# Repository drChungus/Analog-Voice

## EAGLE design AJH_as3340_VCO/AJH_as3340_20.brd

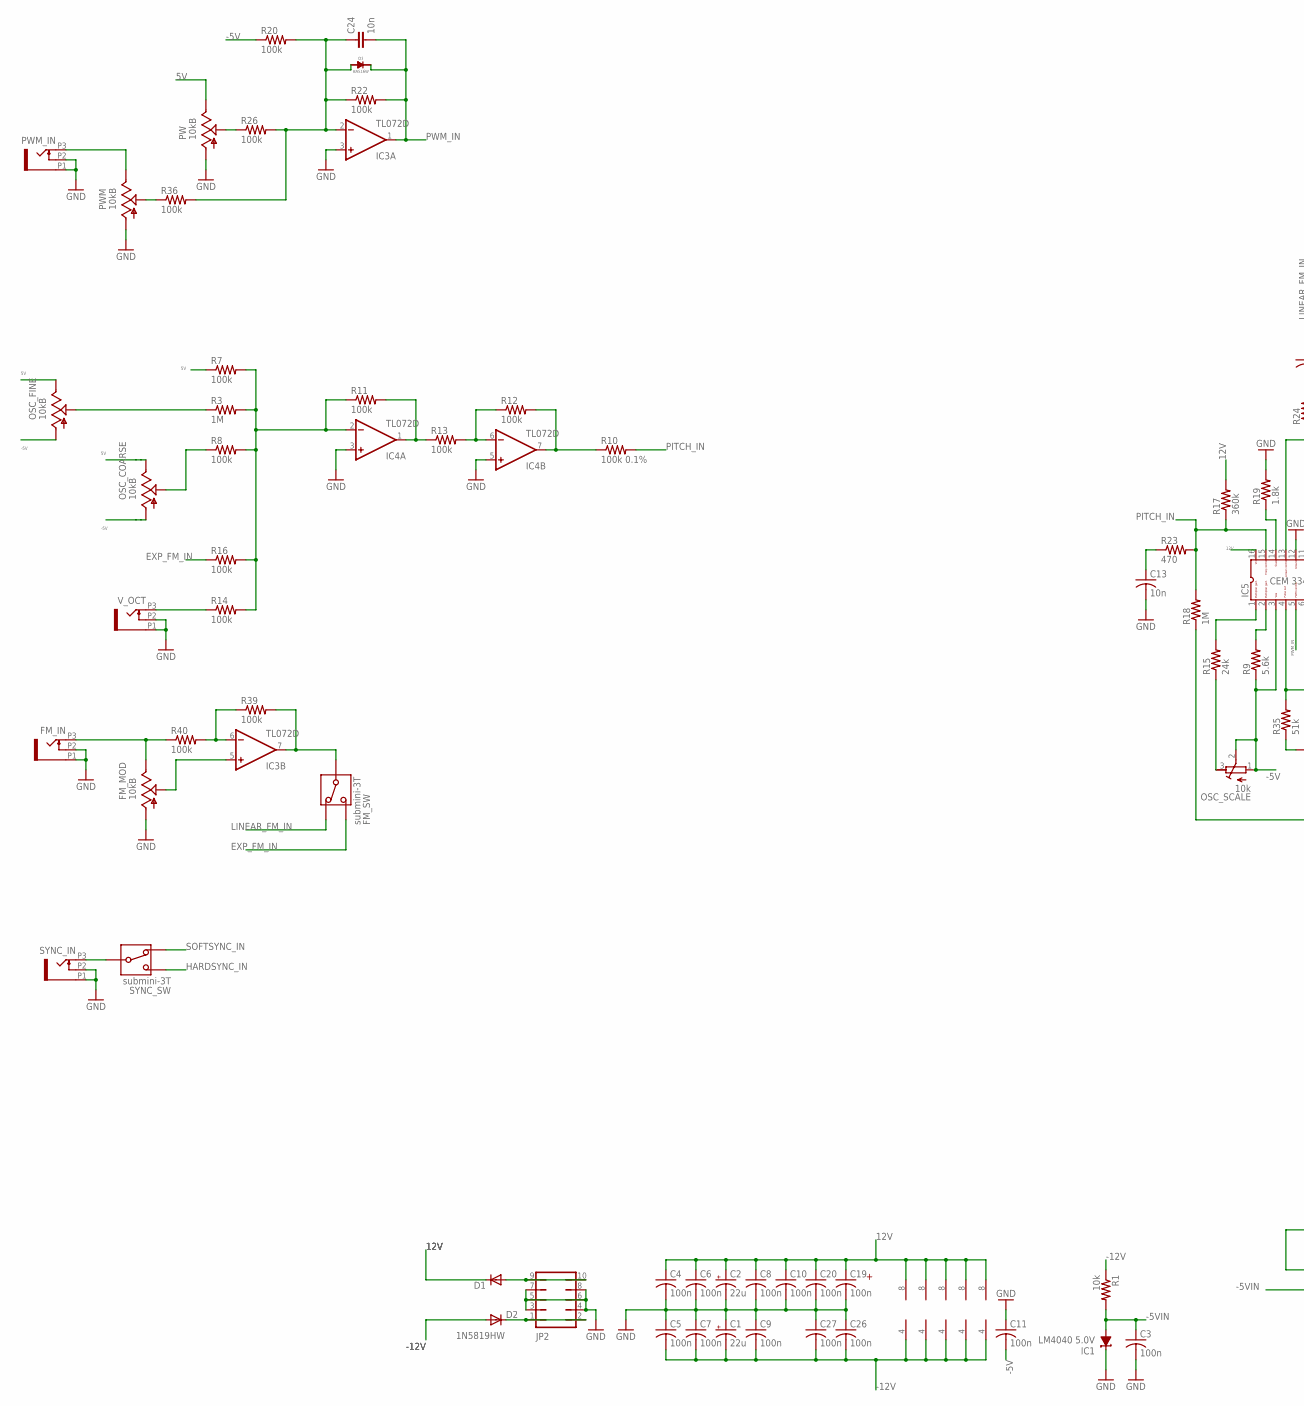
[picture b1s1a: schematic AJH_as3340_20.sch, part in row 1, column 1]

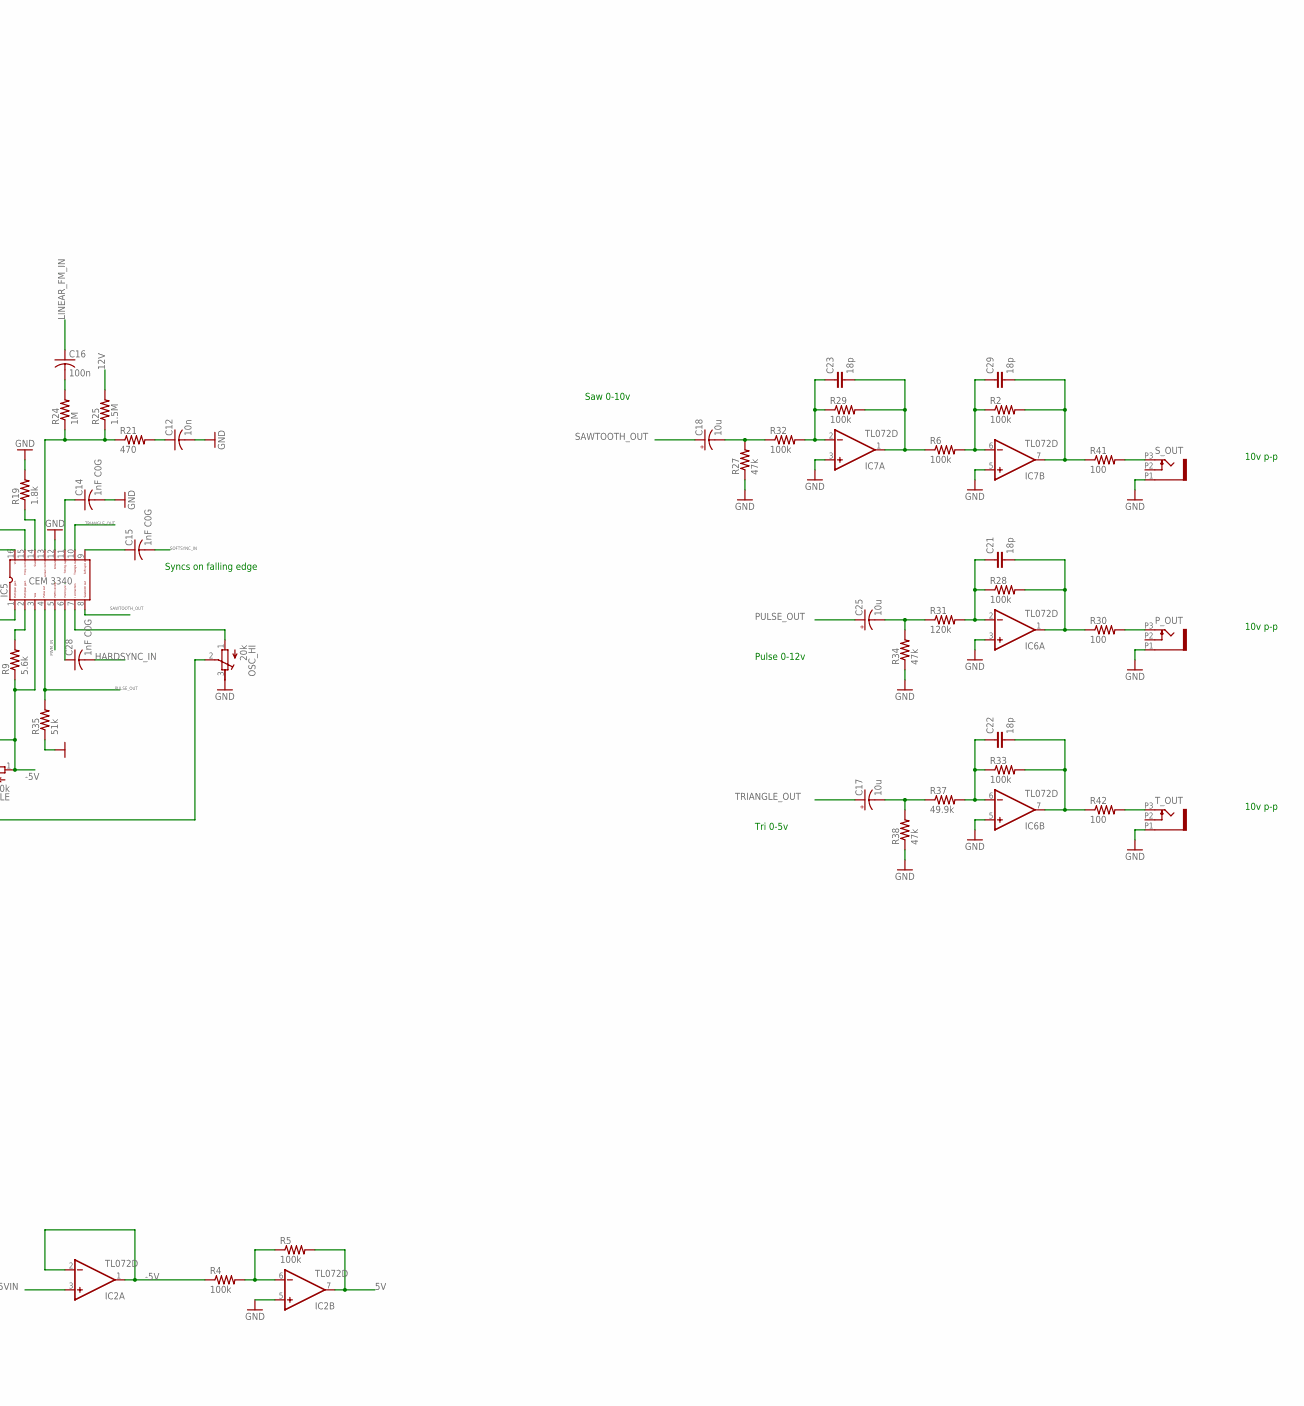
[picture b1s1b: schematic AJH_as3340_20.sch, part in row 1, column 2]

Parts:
C1, C2: 22u; PANASONIC_B
C3, C4, C5, C6, C7, C8, C9, C10, C11, C16, C19, C20, C26, C27: 100n; C0603
C12, C13, C24: 10n; C0603
C14, C15, C28: 1nF C0G; C0603
C17, C18, C25: 10u; PANASONIC_B
C21, C22, C23, C29: 18p; C0603
D1, D2: 1N5819HW; SOD123
D3: BAS16W; SOT-323
FM_IN: PJ301_THONKICONN6; WQP_PJ_301M6
FM_MOD: 10kB; ALPS_POT_VERTICAL_PS
FM_SW: submini-3T; SPDT-SUB
IC1: LM4040 5.0V; DBZ_R-PDSO-G3
IC2, IC3, IC4, IC6, IC7: TL072D; SO08
IC5: CEM3340SOIC16; SO16
JP2: JP5Q
OSC_COARSE: 10kB; ALPS_POT_VERTICAL
OSC_FINE: 10kB; ALPS_POT_VERTICAL
OSC_HI: 20k; RTRIM3296X
OSC_SCALE: 10k; RTRIM3296X
PW: 10kB; ALPS_POT_VERTICAL_PS
PWM: 10kB; ALPS_POT_VERTICAL_PS
PWM_IN: PJ301_THONKICONN6; WQP_PJ_301M6
P_OUT: PJ301_THONKICONN6; WQP_PJ_301M6
R1: 10k; R0603
R2, R4, R5, R6, R7, R8, R11, R12, R13, R14, R16, R20, R22, R26, R28, R29, R32, R33, R36, R39, R40: 100k; R0603
R3, R18, R24: 1M; R0603
R9: 5.6k; R0603
R10: 100k 0.1%; R0603
R15: 24k; R0603
R17: 360k; R0603
R19: 1.8k; R0603
R21, R23: 470; R0603
R25: 1.5M; R0603
R27, R34, R38: 47k; R0603
R30, R41, R42: 100; R0603
R31: 120k; R0603
R35: 51k; R0603
R37: 49.9k; R0603
SYNC_IN: PJ301_THONKICONN6; WQP_PJ_301M6
SYNC_SW: submini-3T; SPDT-SUB
S_OUT: PJ301_THONKICONN6; WQP_PJ_301M6
T_OUT: PJ301_THONKICONN6; WQP_PJ_301M6
V_OCT: PJ301_THONKICONN6; WQP_PJ_301M6

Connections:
5V: IC2.7 (OUT), OSC_COARSE.P$1 (E), OSC_FINE.P$1 (E), PW.P$1 (E), R5.2, R7.1
12V: C2.+, C4.1, C6.1, C8.1, C10.1, C19.1, C20.1, D1.C, IC2.8 (V+), IC3.8 (V+), IC4.8 (V+), IC5.16, IC6.8 (V+), IC7.8 (V+), R17.2, R25.2
-5V: C11.2, IC2.1 (OUT), IC2.2 (-IN), IC5.3, OSC_COARSE.P$3 (A), OSC_FINE.P$3 (A), OSC_SCALE.1 (E), OSC_SCALE.2 (S), R4.1, R9.1, R20.1
-5VIN: C3.1, IC1.2 (A), IC2.3 (+IN), R1.2
-12V: C1.-, C5.2, C7.2, C9.2, C26.2, C27.2, D2.A, IC2.4 (V-), IC3.4 (V-), IC4.4 (V-), IC6.4 (V-), IC7.4 (V-), R1.1
EXP_FM_IN: FM_SW.P$1, R16.1
GND: C1.+, C2.-, C3.2, C4.2, C5.1, C6.2, C7.1, C8.2, C9.1, C10.2, C11.1, C12.2, C13.2, C14.2, C19.2, C20.2, C26.1, C27.1, FM_IN.P1 (1), FM_IN.P2 (2), FM_MOD.P$3 (A), IC1.1 (C), IC2.5 (+IN), IC3.3 (+IN), IC4.3 (+IN), IC4.5 (+IN), IC5.12, IC6.3 (+IN), IC6.5 (+IN), IC7.3 (+IN), IC7.5 (+IN), JP2.3, JP2.4, JP2.5, JP2.6, JP2.7, JP2.8, OSC_HI.3 (A), PW.P$3 (A), PWM.P$3 (A), PWM_IN.P1 (1), PWM_IN.P2 (2), P_OUT.P1 (1), R19.2, R27.1, R34.1, R35.1, R38.1, SYNC_IN.P1 (1), SYNC_IN.P2 (2), S_OUT.P1 (1), T_OUT.P1 (1), V_OCT.P1 (1), V_OCT.P2 (2)
HARDSYNC_IN: C28.2, SYNC_SW.P$1
LINEAR_FM_IN: C16.1, FM_SW.P$3
MAIN_CV1: PWM.P$1 (E), PWM_IN.P3 (3)
unnamed: PW.P$2 (S), R26.1
unnamed: R41.2, S_OUT.P3 (3)
unnamed: FM_MOD.P$2 (S), IC3.5 (+IN)
unnamed: OSC_COARSE.P$2 (S), R8.1
unnamed: IC3.6 (-IN), R39.1, R40.2
unnamed: D1.A, JP2.9, JP2.10
unnamed: IC4.2 (-IN), R3.2, R7.2, R8.2, R11.1, R14.2, R16.2
unnamed: IC4.1 (OUT), R11.2, R13.1
unnamed: IC4.6 (-IN), R12.1, R13.2
unnamed: R14.1, V_OCT.P3 (3)
unnamed: OSC_FINE.P$2 (S), R3.1
unnamed: FM_SW.P$2, IC3.7 (OUT), R39.2
unnamed: IC2.6 (-IN), R4.2, R5.1
unnamed: P_OUT.P3 (3), R30.2
unnamed: C29.1, IC7.6 (-IN), R2.1, R6.2
unnamed: R42.2, T_OUT.P3 (3)
unnamed: C18.-, R27.2, R32.1
unnamed: C25.-, R31.1, R34.2
unnamed: C17.-, R37.1, R38.2
unnamed: D2.C, JP2.1, JP2.2
unnamed: C23.1, IC7.2 (-IN), R29.1, R32.2
unnamed: C23.2, IC7.1 (OUT), R6.1, R29.2
unnamed: C21.2, IC6.1 (OUT), R28.2, R30.1
unnamed: C22.2, IC6.7 (OUT), R33.2, R42.1
unnamed: C22.1, IC6.6 (-IN), R33.1, R37.2
unnamed: C21.1, IC6.2 (-IN), R28.1, R31.2
unnamed: C15.1, IC5.9
unnamed: C13.1, R23.1
unnamed: OSC_HI.2 (S), R18.1
unnamed: IC5.1, R15.2
unnamed: OSC_SCALE.3 (A), R15.1
unnamed: IC5.2, R9.2
unnamed: IC5.14, R19.1
unnamed: C14.1, IC5.11
unnamed: C12.1, R21.2
unnamed: IC5.13, R21.1, R24.1, R25.1
unnamed: C16.2, R24.2
unnamed: C29.2, IC7.7 (OUT), R2.2, R41.1
unnamed: FM_IN.P3 (3), FM_MOD.P$1 (E), R40.1
unnamed: C28.1, IC5.6
unnamed: IC5.7, OSC_HI.1 (E)
unnamed: PWM.P$2 (S), R36.1
PITCH_IN: IC5.15, R10.2, R17.1, R18.2, R23.2
PRESUMMED_PITCH: IC4.7 (OUT), R10.1, R12.2
PULSE_OUT: C25.+, IC5.4, R35.2
PWM_2_IN_SUM: C24.1, D3.ANODE, IC3.2 (-IN), R20.2, R22.1, R26.2, R36.2
PWM_IN: C24.2, D3.CATHODE, IC3.1 (OUT), IC5.5, R22.2
SAWTOOTH_OUT: C18.+, IC5.8
SOFTSYNC_IN: C15.2, SYNC_SW.P$3
SYNC_IN: SYNC_IN.P3 (3), SYNC_SW.P$2
TRIANGLE_OUT: C17.+, IC5.10

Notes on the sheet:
10v p-p
Saw 0-10v
Pulse 0-12v
Tri 0-5v
Syncs on falling edge

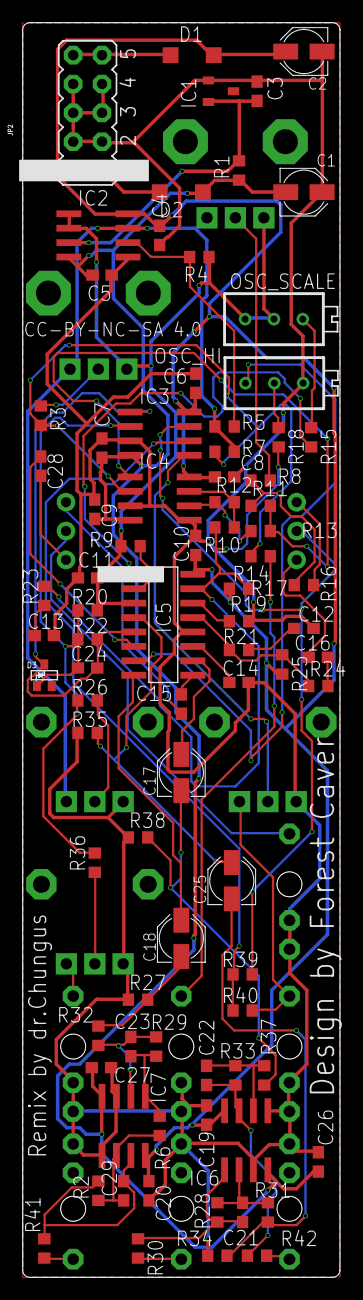
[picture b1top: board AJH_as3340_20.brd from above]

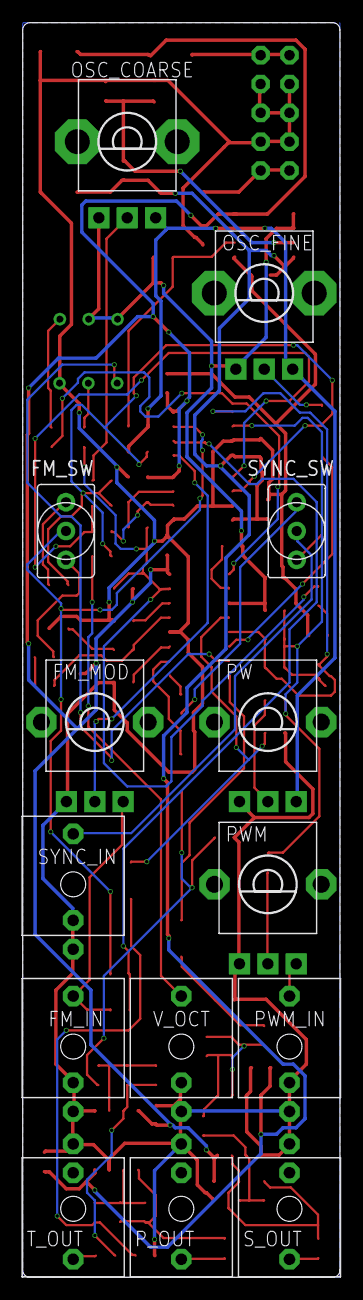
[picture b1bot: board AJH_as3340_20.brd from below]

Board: 2 copper layers, 27.9 x 110.5 mm, 99 parts (14 on the bottom side), 61 nets.

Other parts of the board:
U$1: EURO_PCB_6HP

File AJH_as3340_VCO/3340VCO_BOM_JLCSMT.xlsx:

Comment | Designator | Footprint | JLCPCB Part #（optional）
10kB | OSC_COARSE, OSC_FINE | ALPS_POT_VERTICAL
10kB | FM_MOD, PW, PWM | ALPS_POT_VERTICAL_PS
M05X2PTH | JP1 | AVR_ICSP
100n | C3, C4, C5, C6, C7, C8, C9, C10, C11, C16, C19, C20, C26, C27 | C0603 | C14663
10n | C24 | C0603 | C57112
10n | C12, C13 | C0603 | C57112
18p | C21, C22, C23, C29 | C0603 | C1647
1nF C0G | C14, C15, C28 | C0603 | C1588
LM4040 5.0V | IC1 | DBZ_R-PDSO-G3 | C69316
10u | C17, C18, C25 | PANASONIC_B | C178621
22u | C1, C2 | PANASONIC_B | C249477
1.5M | R25 | R0603 | C4172
1.8k | R19 | R0603 | C4177
100 | R30, R41, R42 | R0603 | C22775
100k | R2, R4, R5, R6, R7, R8, R11, R12, R13, R14, R16, R20, R22, R26, R28, R29, R32, 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 | R0603 | C25803
100k 0.1% | R10 | R0603 | C328672
10k | R1 | R0603 | C25804
120k | R31 | R0603 | C25808
1M | R3, R18, R24 | R0603 | C22935
24k | R15 | R0603 | C23352
360k | R17 | R0603 | C23146
470 | R21, R23 | R0603 | C23179
47k | R27, R34, R38 | R0603 | C25819
49.9k | R37 | R0603 | C23184
5.6k | R9 | R0603 | C23189
51k | R35 | R0603 | C23196
10k | OSC_SCALE | RTRIM3296X | C118955
20k | OSC_HI | RTRIM3296X | C111789
TL072D | IC2, IC3, IC4, IC6, IC7 | SO08 | C6961
CEM3340SOIC16 | IC5 | SO16
1N5819HW | D1, D2 | SOD123 | C82544
BAS16W | D3 | SOT-323 | C56624
submini-3T | FM_SW, SYNC_SW | SPDT-SUB
PJ301_THONKICONN6 | FM_IN, PWM_IN, P_OUT, SYNC_IN, S_OUT, T_OUT, V_OCT | WQP_PJ_301M6

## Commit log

2021-08-06 Picked JLC Parts, Strted new layout
    we are going 6HP, fuck it
2021-08-06 Started Placing components
    No change on schematic, hella more dense on layout
2021-08-06 Added Art Deco Panel template
2021-08-06 Arranged parts to grid
2021-08-09 Arranged UI
2021-08-09 Fixed FP objects
2021-08-09 Mirrored holes to FP
    UI DESIGN FREEZE!!
2021-08-17 Routing Done
    Routed the PCB, no components modification is allowed!
2021-08-17 TestFit
    Created gerber and alligned pnp file
2021-08-17 Deleted Temp files
2021-08-17 No mods
2021-08-18 Binary Changes
2021-08-18 New aesthetics
2021-08-25 Finalized Panel
    Adjusted Text for middle sized knobs
2021-08-26 Refined Panel Design
2021-08-26 Finalized PCB
2021-08-27 Added frame to image
2021-09-16 Deleted deprecated Gerber files
2021-09-17 ReColored Panel
2021-09-27 Added Photoshooting Images
2021-09-29 Added Product Images
2021-09-29 Added Compressed product images

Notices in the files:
AJH_as3340_VCO/AJH_as3340_20.brd:
CC-BY-NC-SA 4.0
